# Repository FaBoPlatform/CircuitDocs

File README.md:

Circuit Docs
=======

自作基板のWorkshopです。

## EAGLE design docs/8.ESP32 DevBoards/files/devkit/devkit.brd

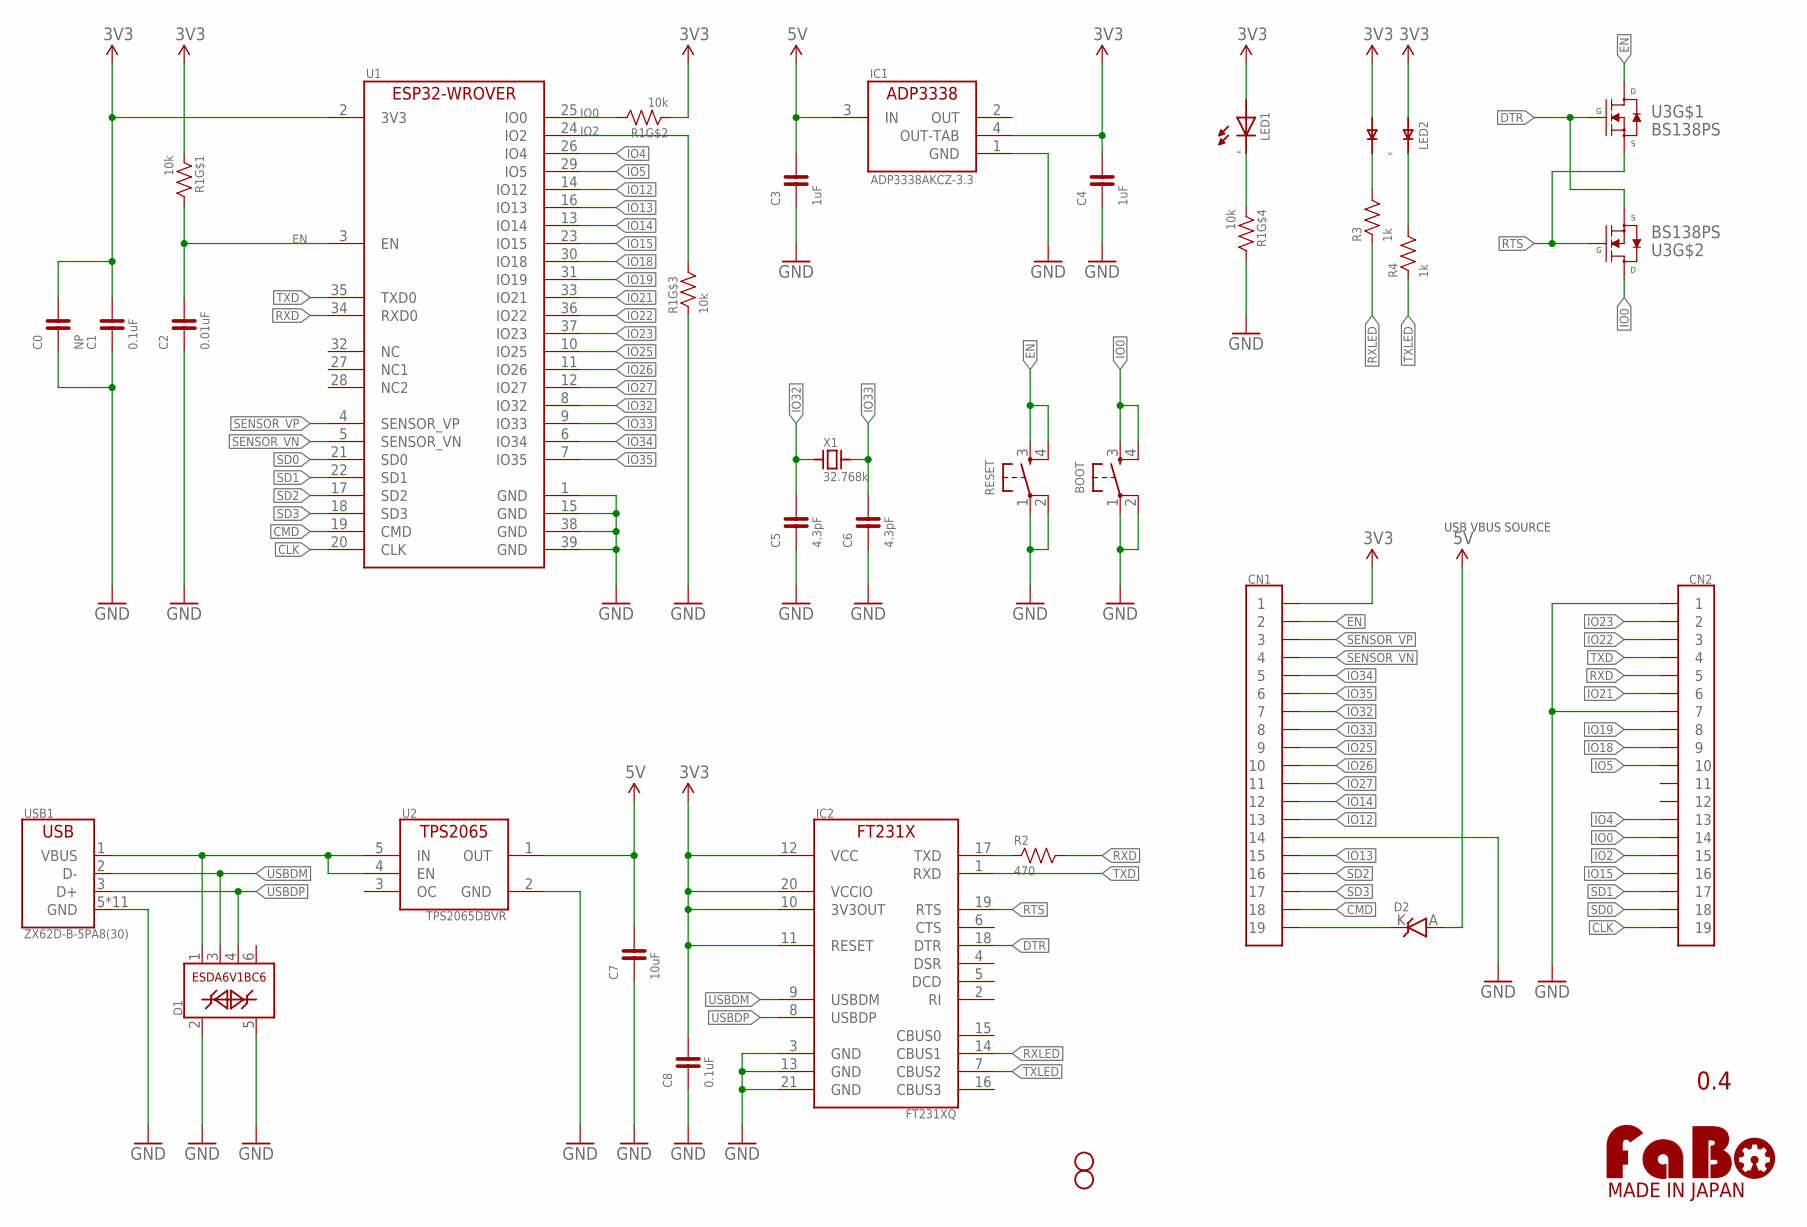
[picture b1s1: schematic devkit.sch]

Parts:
BOOT: TACTILE-KMR2; KMR2-TACT
C0: NP; MULTIPAD0603
C1, C8: 0.1uF; EIA0603
C2: 0.01uF; EIA0603
C3, C4: 1uF; EIA0603
C5, C6: 4.3pF; EIA0603
C7: 10uF; EIA0603
CN1, CN2: PIN_1X19
D1: ESDA6V1BC6; SOT-23-6L
D2: DIODE_SCHOTTKY-RB161MM-20; SOD-123FL_RB161MM-20
FID1, FID2: FIDUCIAL-TOP; FIDUCIAL_15_TOP
IC1: ADP3338AKCZ-3.3; SOT-223-KC3
IC2: FT231XQ; QFN-20
LED1: LED-0603; LED_0603
LED2: HSMF-C16X
LOGO1: LOGO_FABO-M_BOTTOM; LOGO_FABO_M_BOTTOM
R1: 10k; EXBV8V
R2: 470; EIA0603
R3, R4: 1k; EIA0603
RESET: TACTILE-KMR2; KMR2-TACT
U1: ESP32-WROVER-B
U2: TPS2065DBVR; SOT-23-5
U3: BS138PS; SOT-363
USB1: ZX62D-B-5PA8(30); ZX62D-B-5PA8
X1: 32.768k; ABS07

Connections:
3V3: C0.2, C1.2, C4.2, C8.2, CN1.1, IC1.4 (OUT-TAB), IC2.10 (3V3OUT), IC2.11 (RESET), IC2.12 (VCC), IC2.20 (VCCIO), LED1.A (ANODE), LED2.1 (A1), LED2.2 (A2), R1.1, R1.2 (1), U1.2 (3V3)
5V: C3.2, C7.2, D2.A, IC1.3 (IN), U2.1 (OUT)
CLK: CN2.19, U1.20 (CLK)
CMD: CN1.18, U1.19 (CMD)
DTR: IC2.18 (DTR), U3.2 (G), U3.4 (S)
EN: C2.2, CN1.2, R1.8 (2), RESET.3, RESET.4, U1.3 (EN), U3.6 (D)
GND: BOOT.1, BOOT.2, C0.1, C1.1, C2.1, C3.1, C4.1, C5.1, C6.1, C7.1, C8.1, CN1.14, CN2.1, CN2.7, D1.2, D1.5, IC1.1 (GND), IC2.3 (GND), IC2.13 (GND), IC2.21 (GND), R1.3 (1), R1.5 (2), RESET.1, RESET.2, U1.1 (GND), U1.15 (GND), U1.38 (GND), U1.39 (GND), U2.2 (GND), USB1.5 (GND), USB1.B1 (GND), USB1.B2 (GND), USB1.B3 (GND), USB1.B4 (GND), USB1.T1 (GND), USB1.T2 (GND), USB1.T3 (GND), USB1.T4 (GND), USB1.T5 (GND), USB1.T6 (GND)
IO0: BOOT.3, BOOT.4, CN2.14, R1.7 (2), U1.25 (IO0), U3.3 (D)
IO2: CN2.15, R1.6 (2), U1.24 (IO2)
IO4: CN2.13, U1.26 (IO4)
IO5: CN2.10, U1.29 (IO5)
IO12: CN1.13, U1.14 (IO12)
IO13: CN1.15, U1.16 (IO13)
IO14: CN1.12, U1.13 (IO14)
IO15: CN2.16, U1.23 (IO15)
IO18: CN2.9, U1.30 (IO18)
IO19: CN2.8, U1.31 (IO19)
IO21: CN2.6, U1.33 (IO21)
IO22: CN2.3, U1.36 (IO22)
IO23: CN2.2, U1.37 (IO23)
IO25: CN1.9, U1.10 (IO25)
IO26: CN1.10, U1.11 (IO26)
IO27: CN1.11, U1.12 (IO27)
IO32: C5.2, CN1.7, U1.8 (IO32), X1.1
IO33: C6.2, CN1.8, U1.9 (IO33), X1.2
IO34: CN1.5, U1.6 (IO34)
IO35: CN1.6, U1.7 (IO35)
LED1K: LED1.K (CATHODE), R1.4 (1)
LED2K1: LED2.4 (K2), R3.2
LED2K2: LED2.3 (K1), R4.2
OUT5V: CN1.19, D2.K
RTS: IC2.19 (RTS), U3.1 (S), U3.5 (G)
RXD: CN2.5, R2.2, U1.34 (RXD0)
RXLED: IC2.14 (CBUS1), R3.1
SD0: CN2.18, U1.21 (SD0)
SD1: CN2.17, U1.22 (SD1)
SD2: CN1.16, U1.17 (SD2)
SD3: CN1.17, U1.18 (SD3)
SENSOR_VN: CN1.4, U1.5 (SENSOR_VN)
SENSOR_VP: CN1.3, U1.4 (SENSOR_VP)
TXD: CN2.4, IC2.1 (RXD), U1.35 (TXD0)
TXLED: IC2.7 (CBUS2), R4.1
TXPIN: IC2.17 (TXD), R2.1
USBDM: D1.3, IC2.9 (USBDM), USB1.2 (D-)
USBDP: D1.4, IC2.8 (USBDP), USB1.3 (D+)
USBVBUS: D1.1, U2.4 (EN), U2.5 (IN), USB1.1 (VBUS)

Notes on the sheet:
0.4
USB VBUS SOURCE

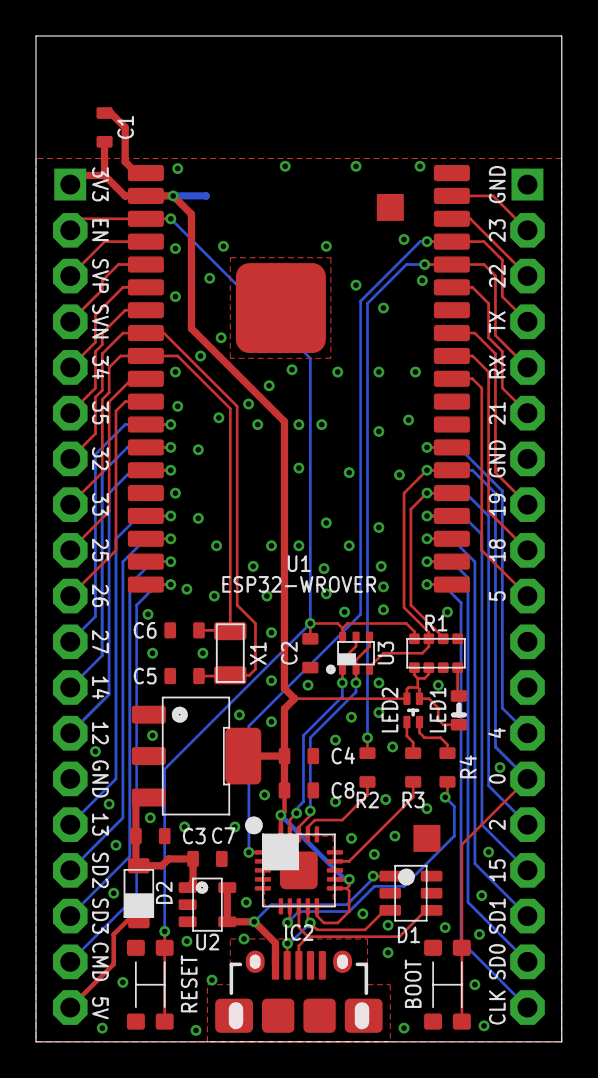
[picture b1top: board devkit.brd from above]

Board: 2 copper layers, 29.2 x 55.9 mm, 31 parts (1 on the bottom side), 46 nets.

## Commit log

2017-02-18 Update CircuitDocs.
2017-02-18 Update circuit.
2017-02-19 Update voltera.
2017-02-19 Update Board.
2017-02-19 Update baord.
2017-06-22 Update docs.
2017-06-22 Update Color LED.
2017-06-22 Update summary.
2017-06-22 Update setting.
2017-06-22 Update Arduino Base.
2017-06-22 Update regulator.
2017-06-22 Update Arduino.
2017-06-22 Add PCB.
2018-12-14 Deployed 2ab0cd6 with MkDocs version: 1.0.4
2018-12-16 Update for MKDocs.
2018-12-16 Deployed 27111ef with MkDocs version: 1.0.4
2018-12-16 Deployed 65c6019 with MkDocs version: 1.0.4
2018-12-16 Update md.
2018-12-17 Deployed 3092e84 with MkDocs version: 1.0.4
2018-12-17 Chipmounter_First_Commit
2018-12-17 Second_Update.
2018-12-17 Update eagle.
2018-12-17 Deployed 0b4363e with MkDocs version: 1.0.4
2018-12-17 third_update
2018-12-17 Deployed ddaf9d8 with MkDocs version: 1.0.4
2018-12-17 Deployed 2a7d28a with MkDocs version: 1.0.4
2018-12-17 forth_update.
2018-12-17 add ESP32 DevBoadrd
2018-12-17 rm DS_Store
2018-12-18 Update .
2018-12-18 Deployed 11abbcb with MkDocs version: 1.0.4
2018-12-18 rename ESP32 part
2018-12-18 Deployed 03c53e0 with MkDocs version: 1.0.4
2018-12-18 Deployed 9031857 with MkDocs version: 1.0.4
2018-12-18 Deployed 840f9b8 with MkDocs version: 1.0.4
2018-12-18 add ESP32 DevBoards
2018-12-18 Ktemp_Arduino_SourceCode_addtion.
2018-12-18 reflow_temprature_insepection.
2018-12-18 Deployed 3e32bd7 with MkDocs version: 1.0.4
2018-12-19 Update.gitignore.
2018-12-19 Deployed b4ba4ff with MkDocs version: 1.0.4
2018-12-19 EAGLE_BOM_LIST
2018-12-19 Numbering.
2018-12-19 Numbering_2
2018-12-19 update6.
2018-12-19 Deployed 4da4e77 with MkDocs version: 1.0.4
2018-12-19 update6
2018-12-19 update7
2018-12-19 update8.
2018-12-20 update8
2018-12-20 Deployed b258570 with MkDocs version: 1.0.4
2018-12-22 Deployed e26027a with MkDocs version: 1.0.4
2018-12-22 Deployed 925a875 with MkDocs version: 1.0.4
2018-12-25 Update denbun.
2019-02-23 Deployed 599dab6 with MkDocs version: 1.0.4
2020-07-08 Deployed 599dab6 with MkDocs version: 1.1
2020-07-08 MKDOCSの更新。

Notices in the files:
parts and their libraries:
component: Released under the Creative Commons
component: https://creativecommons.org/licenses/by-sa/4.0
